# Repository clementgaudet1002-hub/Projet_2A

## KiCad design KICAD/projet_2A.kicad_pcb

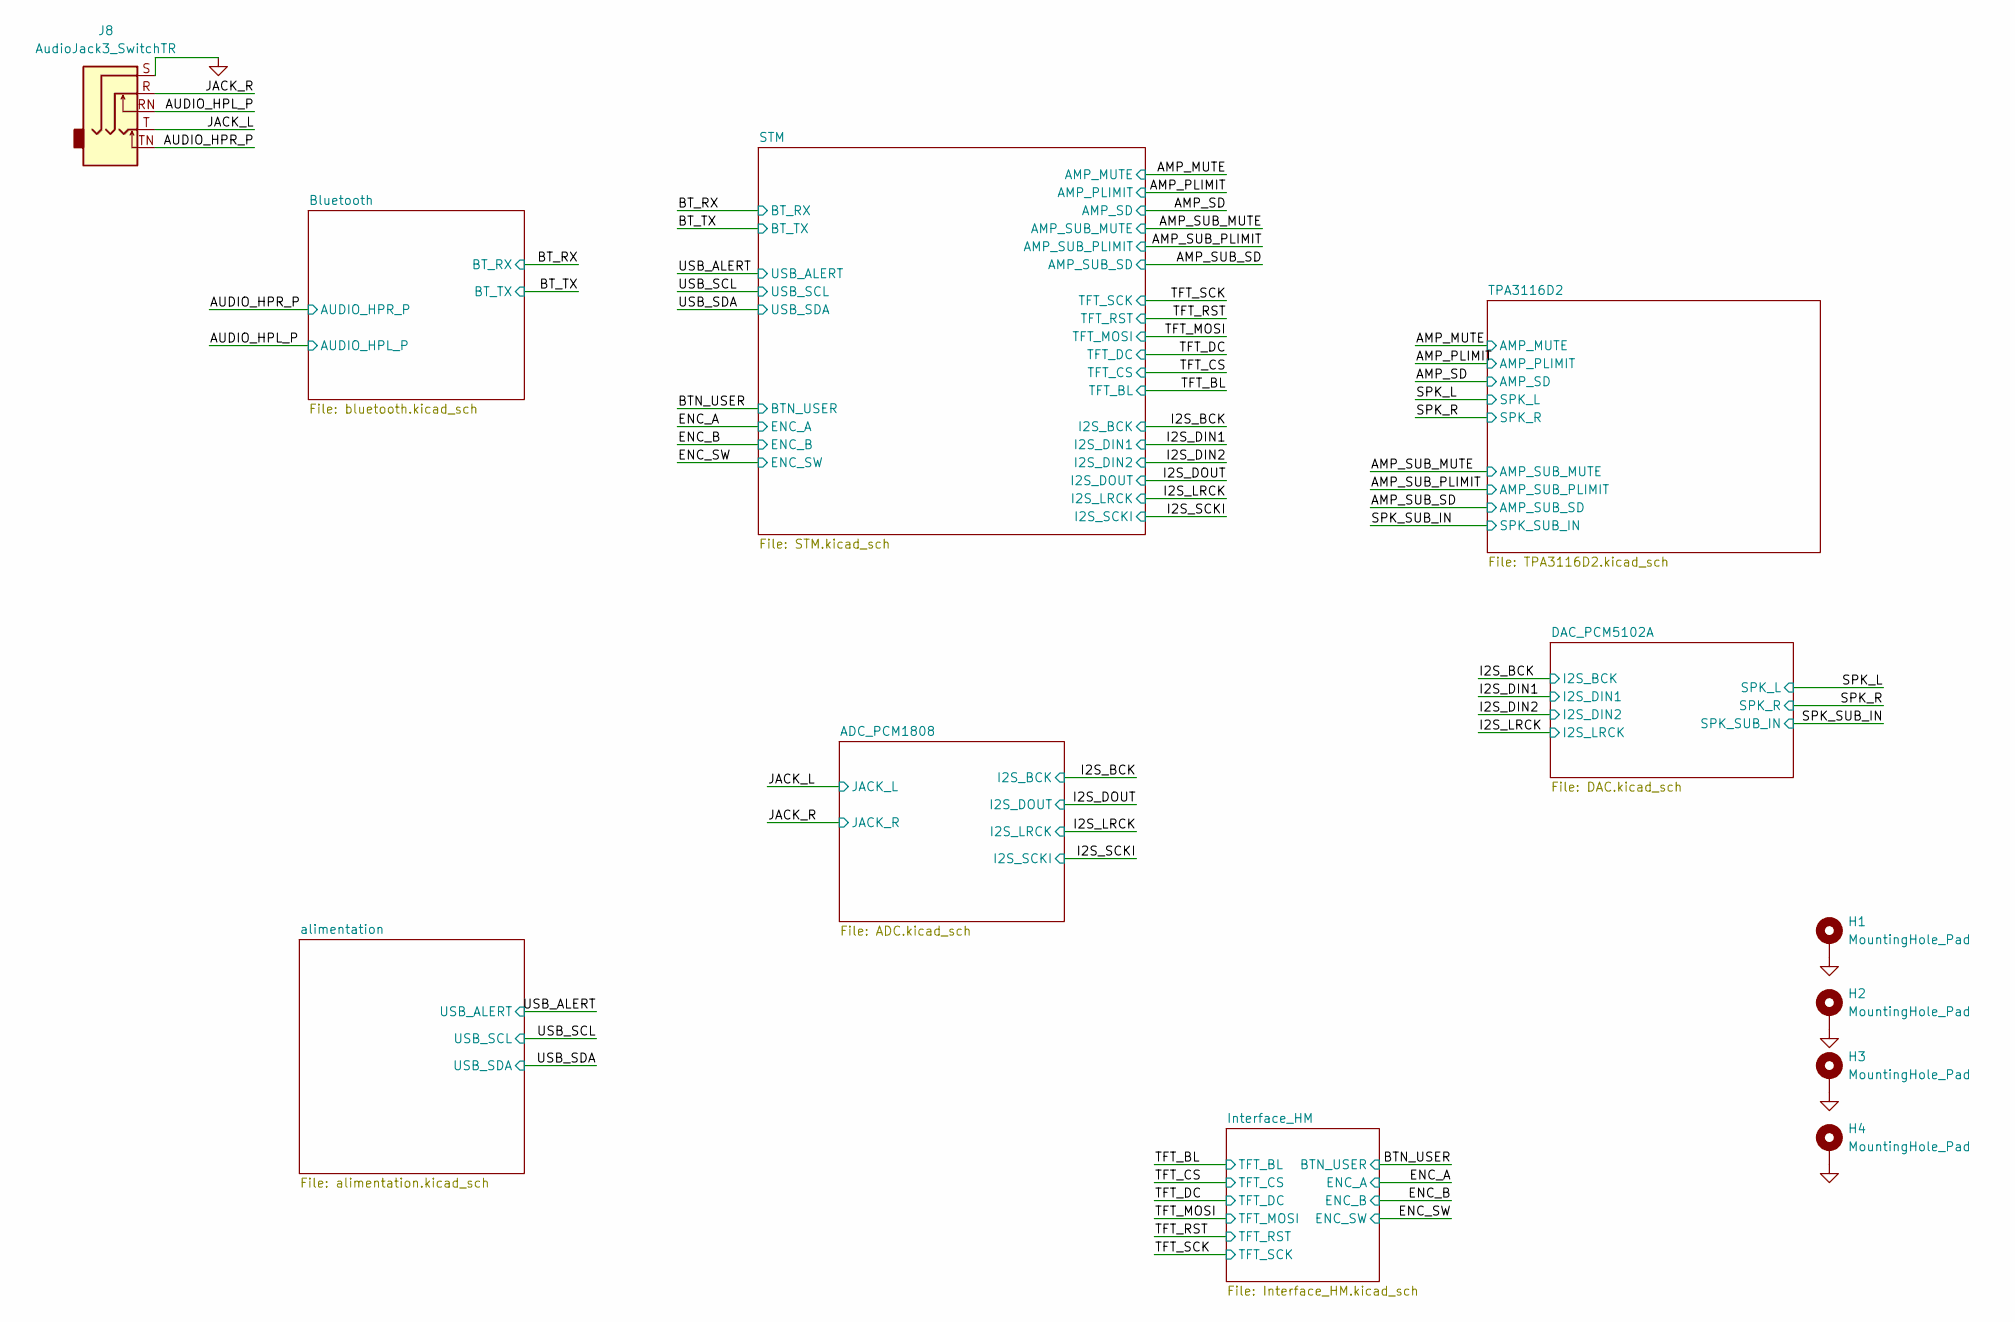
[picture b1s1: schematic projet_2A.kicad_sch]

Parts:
H1, H2, H3, H4: MountingHole_Pad; MountingHole_2.2mm_M2_Pad_TopBottom
J8: AudioJack3_SwitchTR; Jack_3.5mm_Ledino_KB3SPRS_Horizontal

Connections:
/AUDIO_HPL_P: J8.RN; also elsewhere on the board
/AUDIO_HPR_P: J8.TN; also elsewhere on the board
/JACK_L: J8.T; also elsewhere on the board
/JACK_R: J8.R; also elsewhere on the board
GND: H1.1 (1_1), H2.1 (1_1), H3.1 (1_1), H4.1 (1_1), J8.S; also elsewhere on the board

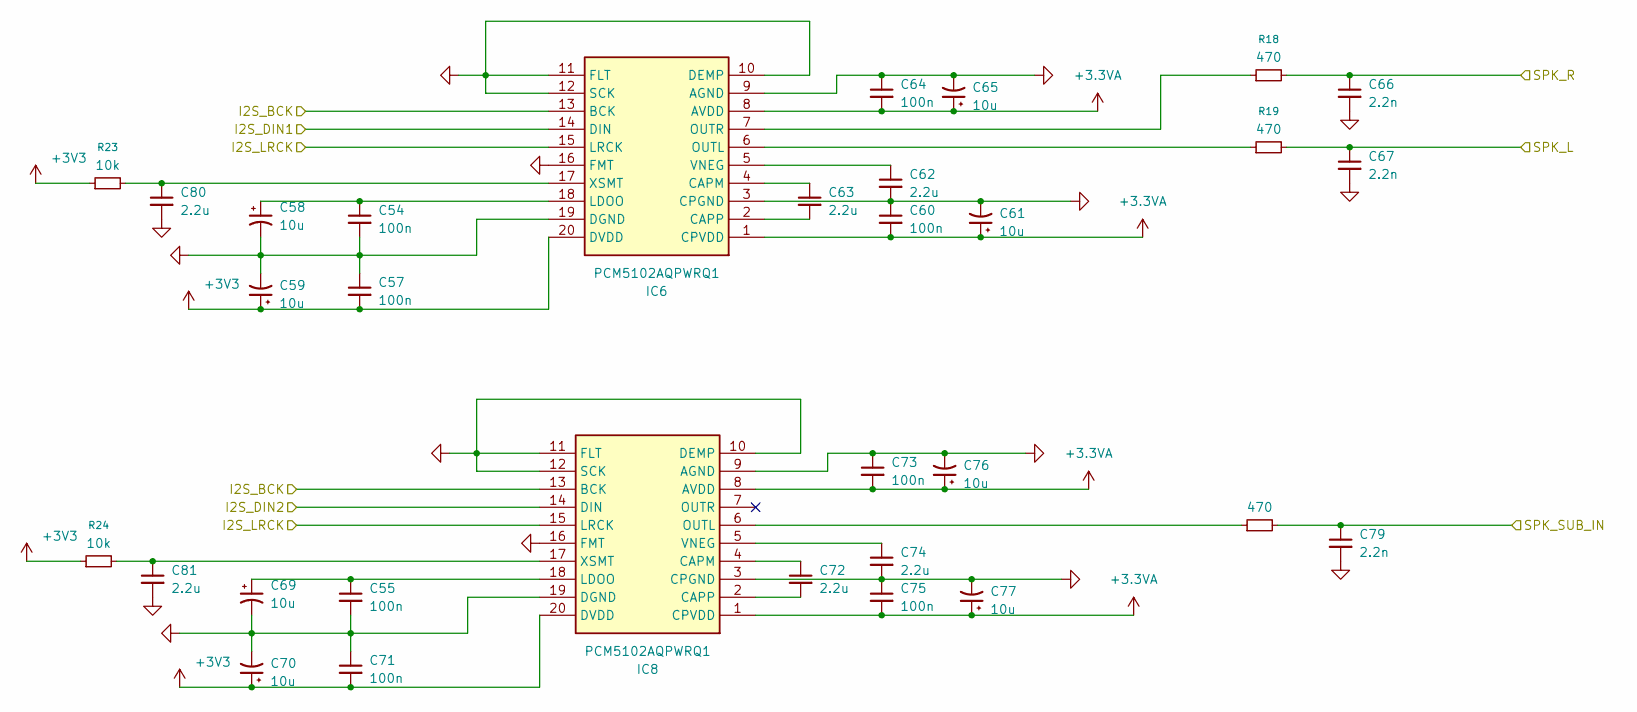
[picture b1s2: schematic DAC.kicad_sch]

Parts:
C54, C55, C57, C60, C64, C71, C73, C75: 100n; C_0603_1608Metric
C58, C59, C61, C65, C69, C70, C76, C77: 10u; C_1206_3216Metric
C62, C63, C72, C74, C80, C81: 2.2u; C_1206_3216Metric
C66, C67, C79: 2.2n; C_0603_1608Metric
IC6, IC8: PCM5102AQPWRQ1; Manufacturer_Part_Number PCM5102AQPWRQ1; Mouser Part Number 595-PCM5102AQPWRQ1
R18, R19, R22: 470; R_0603_1608Metric
R23, R24: 10k; R_0603_1608Metric

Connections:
+3.3VA: C60.2, C61.1, C64.2, C65.1, C73.2, C75.2, C76.1, C77.1, IC6.1 (CPVDD), IC6.8 (AVDD), IC8.1 (CPVDD), IC8.8 (AVDD); also elsewhere on the board
+3V3: C57.2, C59.1, C70.1, C71.2, IC6.20 (DVDD), IC8.20 (DVDD), R23.1, R24.1; also elsewhere on the board
/I2S_BCK: IC6.13 (BCK), IC8.13 (BCK); also elsewhere on the board
/I2S_DIN1: IC6.14 (DIN); also elsewhere on the board
/I2S_DIN2: IC8.14 (DIN); also elsewhere on the board
/I2S_LRCK: IC6.15 (LRCK), IC8.15 (LRCK); also elsewhere on the board
/SPK_L: C67.1, R19.2; also elsewhere on the board
/SPK_R: C66.1, R18.2; also elsewhere on the board
/SPK_SUB_IN: C79.1, R22.2; also elsewhere on the board
GND: C54.2, C55.2, C57.1, C58.2, C59.2, C60.1, C61.2, C62.2, C64.1, C65.2, C66.2, C67.2, C69.2, C70.2, C71.1, C73.1, C74.2, C75.1, C76.2, C77.2, C79.2, C80.2, C81.2, IC6.3 (CPGND), IC6.9 (AGND), IC6.10 (DEMP), IC6.11 (FLT), IC6.12 (SCK), IC6.16 (FMT), IC6.19 (DGND), IC8.3 (CPGND), IC8.9 (AGND), IC8.10 (DEMP), IC8.11 (FLT), IC8.12 (SCK), IC8.16 (FMT), IC8.19 (DGND); also elsewhere on the board
unnamed: C63.1, IC6.4 (CAPM)
unnamed: C63.2, IC6.2 (CAPP)
unnamed: C54.1, C58.1, IC6.18 (LDOO)
unnamed: IC6.6 (OUTL), R19.1
unnamed: IC6.7 (OUTR), R18.1
unnamed: C62.1, IC6.5 (VNEG)
unnamed: C80.1, IC6.17 (XSMT), R23.2
unnamed: C72.1, IC8.4 (CAPM)
unnamed: C72.2, IC8.2 (CAPP)
unnamed: C55.1, C69.1, IC8.18 (LDOO)
unnamed: IC8.6 (OUTL), R22.1
unnamed: C74.1, IC8.5 (VNEG)
unnamed: C81.1, IC8.17 (XSMT), R24.2

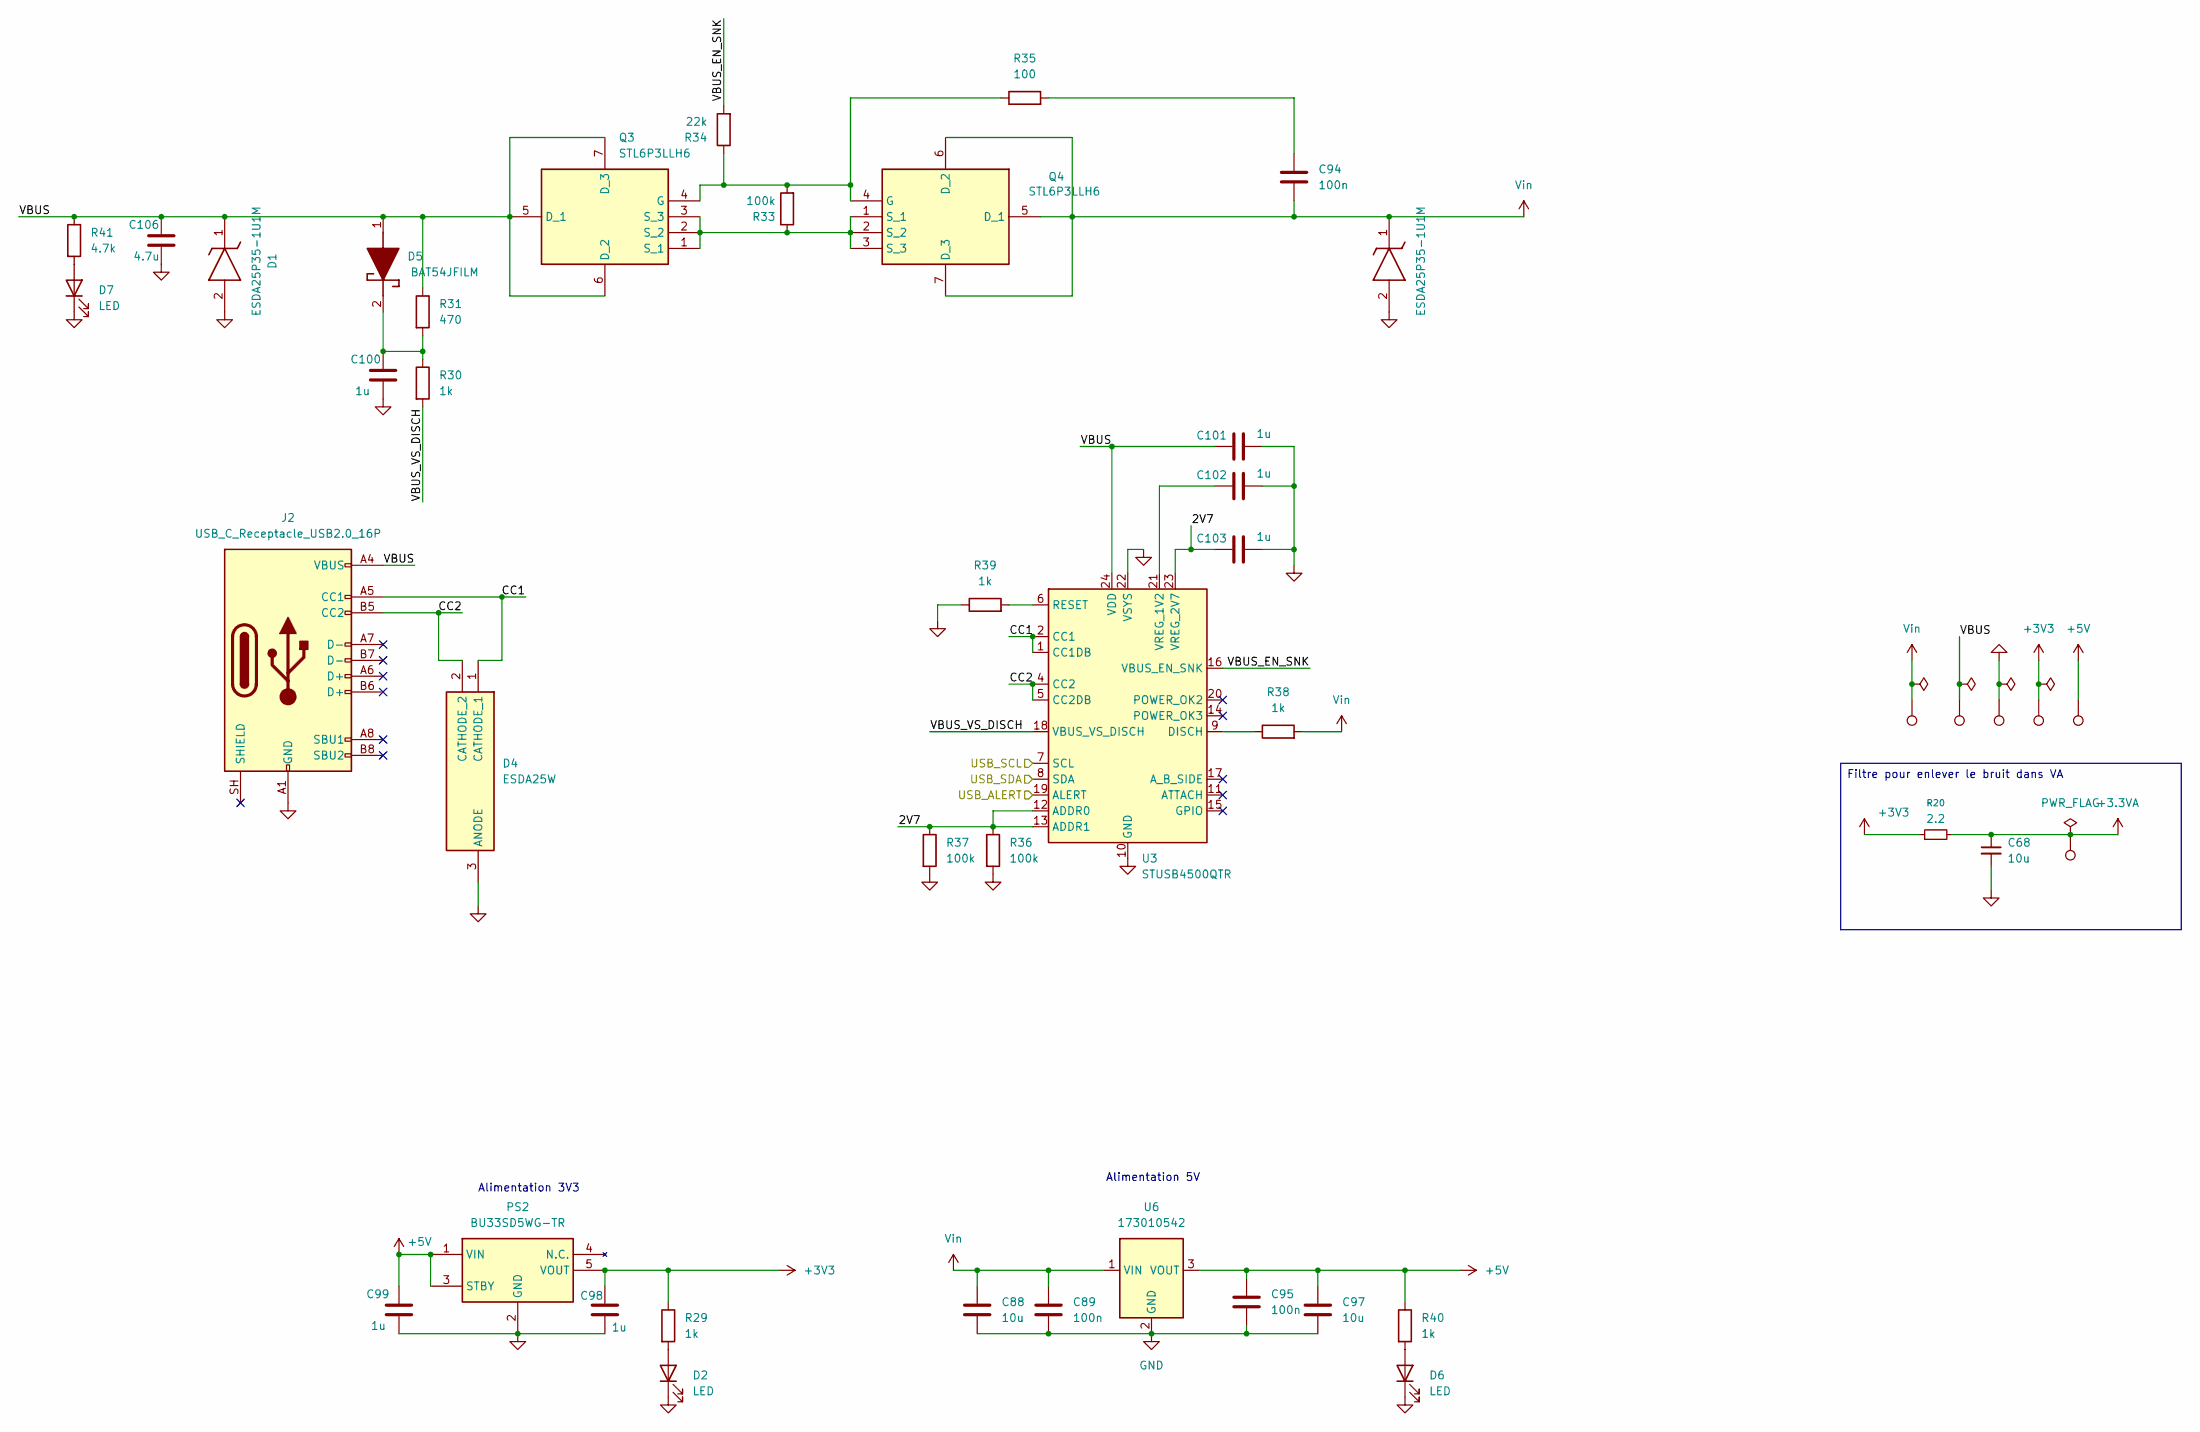
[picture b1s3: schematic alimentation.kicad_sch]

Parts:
C68, C88, C97: 10u; C_1206_3216Metric
C89, C94, C95: 100n; C_0603_1608Metric
C98, C99, C100, C101, C102, C103: 1u; C_0603_1608Metric
C106: 4.7u; C_0603_1608Metric
D1, D3: ESDA25P35-1U1M; ESDA25P351U1M; Mouser Part Number 511-ESDA25P35-1U1M
D2, D6, D7: LED; LED_0603_1608Metric
D4: ESDA25W; Mouser Part Number 511-ESDA25W
D5: BAT54JFILM; Mouser Part Number 511-BAT54JFILM
J2: USB_C_Receptacle_USB2.0_16P; USB_C_Receptacle_GCT_USB4105-xx-A_16P_TopMnt_Horizontal
PS2: BU33SD5WG-TR; Manufacturer_Part_Number BU33SD5WG-TR; Mouser Part Number 755-BU33SD5WG-TR
Q3, Q4: STL6P3LLH6; STL8N10F7; Mouser Part Number 511-STL6P3LLH6
R20: 2.2; R_0603_1608Metric
R29, R30, R38, R39, R40: 1k; R_0603_1608Metric
R31: 470; R_0603_1608Metric
R33, R36, R37: 100k; R_0603_1608Metric
R34: 22k; R_0603_1608Metric
R35: 100; R_0603_1608Metric
R41: 4.7k; R_1206_3216Metric
TP2, TP4, TP5, TP6, TP7, TP8: TestPoint; TestPoint_Pad_D1.5mm
U3: STUSB4500QTR; QFN-24-1EP_4x4mm_P0.5mm_EP2.7x2.7mm
U6: 173010542; U_Wurth_MagIC-FDSM_173010x42

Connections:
+3.3VA: C68.1, R20.2, TP8.1 (1_1); also elsewhere on the board
+3V3: C98.1, PS2.5 (VOUT), R20.1, R29.1, TP6.1 (1_1); also elsewhere on the board
+5V: C95.1, C97.1, C99.1, PS2.1 (VIN), PS2.3 (STBY), R40.1, TP7.1 (1_1), U6.3 (VOUT); also elsewhere on the board
/USB_ALERT: U3.19 (ALERT); also elsewhere on the board
/USB_SCL: U3.7 (SCL); also elsewhere on the board
/USB_SDA: U3.8 (SDA); also elsewhere on the board
/alimentation/2V7: C103.1, R36.1, R37.1, U3.12 (ADDR0), U3.13 (ADDR1), U3.23 (VREG_2V7)
/alimentation/CC1: D4.1 (CATHODE_1), J2.A5 (CC1), U3.1 (CC1DB), U3.2 (CC1)
/alimentation/CC2: D4.2 (CATHODE_2), J2.B5 (CC2), U3.4 (CC2), U3.5 (CC2DB)
/alimentation/VBUS: C101.1, C106.1, D1.1 (K), D5.1 (A), J2.A4 (VBUS), J2.A9 (VBUS), J2.B4 (VBUS), J2.B9 (VBUS), Q3.5 (D_1), Q3.6 (D_2), Q3.7 (D_3), R31.1, R41.1, TP4.1 (1_1), U3.24 (VDD)
/alimentation/VBUS_EN_SNK: R34.2, U3.16 (VBUS_EN_SNK)
/alimentation/VBUS_VS_DISCH: R30.2, U3.18 (VBUS_VS_DISCH)
GND: C68.2, C88.2, C89.2, C95.2, C97.2, C98.2, C99.2, C100.2, C101.2, C102.2, C103.2, C106.2, D1.2 (A), D2.1 (K), D3.2 (A), D4.3 (ANODE), D6.1 (K), D7.1 (K), J2.A1 (GND), J2.A12 (GND), J2.B1 (GND), J2.B12 (GND), PS2.2 (GND), R36.2, R37.2, R39.1, TP5.1 (1_1), U3.10 (GND), U3.22 (VSYS), U3.25 (GND), U6.2 (GND); also elsewhere on the board
unnamed: C94.2, R35.2
unnamed: D2.2 (A), R29.2
unnamed: C100.1, D5.2 (K), R30.1, R31.2
unnamed: D6.2 (A), R40.2
unnamed: D7.2 (A), R41.2
unnamed: Q3.4 (G), Q4.4 (G), R33.2, R34.1, R35.1
unnamed: Q3.1 (S_1), Q3.2 (S_2), Q3.3 (S_3), Q4.1 (S_1), Q4.2 (S_2), Q4.3 (S_3), R33.1
unnamed: R38.1, U3.9 (DISCH)
unnamed: R39.2, U3.6 (RESET)
unnamed: C102.1, U3.21 (VREG_1V2)
Vin: C88.1, C89.1, C94.1, D3.1 (K), Q4.5 (D_1), Q4.6 (D_2), Q4.7 (D_3), R38.2, TP2.1 (1_1), U6.1 (VIN); also elsewhere on the board

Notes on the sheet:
Alimentation 5V
Alimentation 3V3
Filtre pour enlever le bruit dans VA

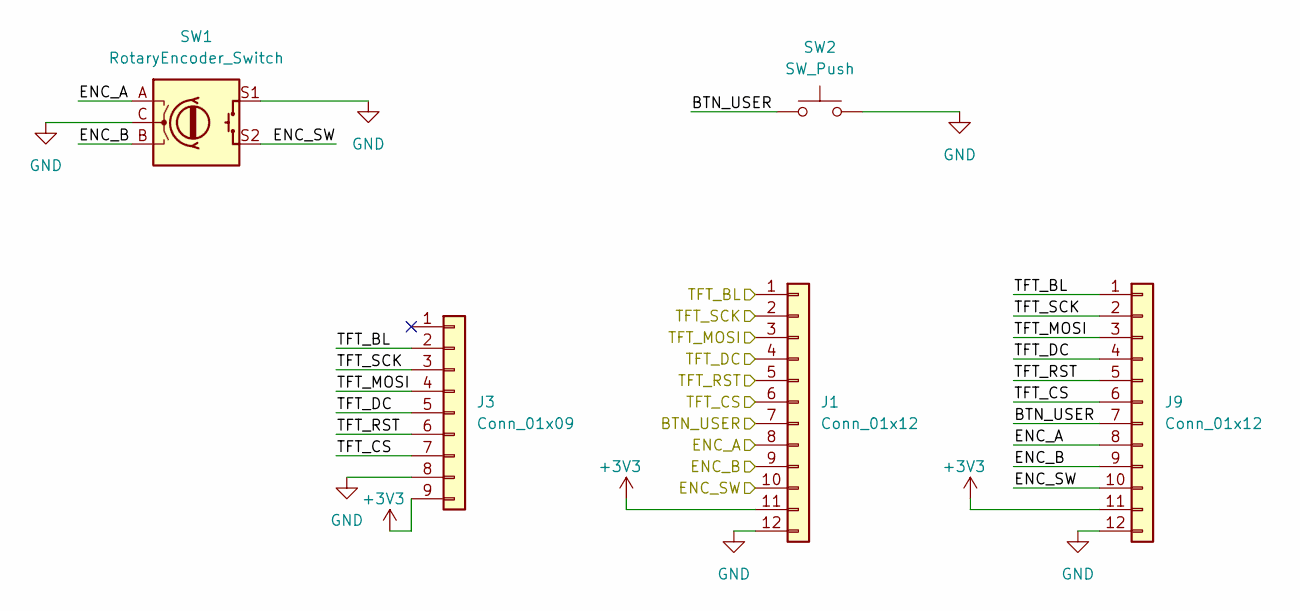
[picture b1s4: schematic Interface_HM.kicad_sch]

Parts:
J1, J9: Conn_01x12; PinHeader_1x12_P2.54mm_Vertical
J3: Conn_01x09; PinHeader_1x09_P2.54mm_Vertical
SW1: RotaryEncoder_Switch; RotaryEncoder_Alps_EC11E-Switch_Vertical_H20mm_CircularMoun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
SW2: SW_Push; SW_PUSH_6mm

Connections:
+3V3: J1.11, J3.9, J9.11; also elsewhere on the board
/BTN_USER: J1.7, J9.7, SW2.1; also elsewhere on the board
/ENC_A: J1.8, J9.8, SW1.A; also elsewhere on the board
/ENC_B: J1.9, J9.9, SW1.B; also elsewhere on the board
/ENC_SW: J1.10, J9.10, SW1.S2; also elsewhere on the board
/TFT_BL: J1.1, J3.2, J9.1; also elsewhere on the board
/TFT_CS: J1.6, J3.7, J9.6; also elsewhere on the board
/TFT_DC: J1.4, J3.5, J9.4; also elsewhere on the board
/TFT_MOSI: J1.3, J3.4, J9.3; also elsewhere on the board
/TFT_RST: J1.5, J3.6, J9.5; also elsewhere on the board
/TFT_SCK: J1.2, J3.3, J9.2; also elsewhere on the board
GND: J1.12, J3.8, J9.12, SW1.C, SW1.S1, SW2.2; also elsewhere on the board

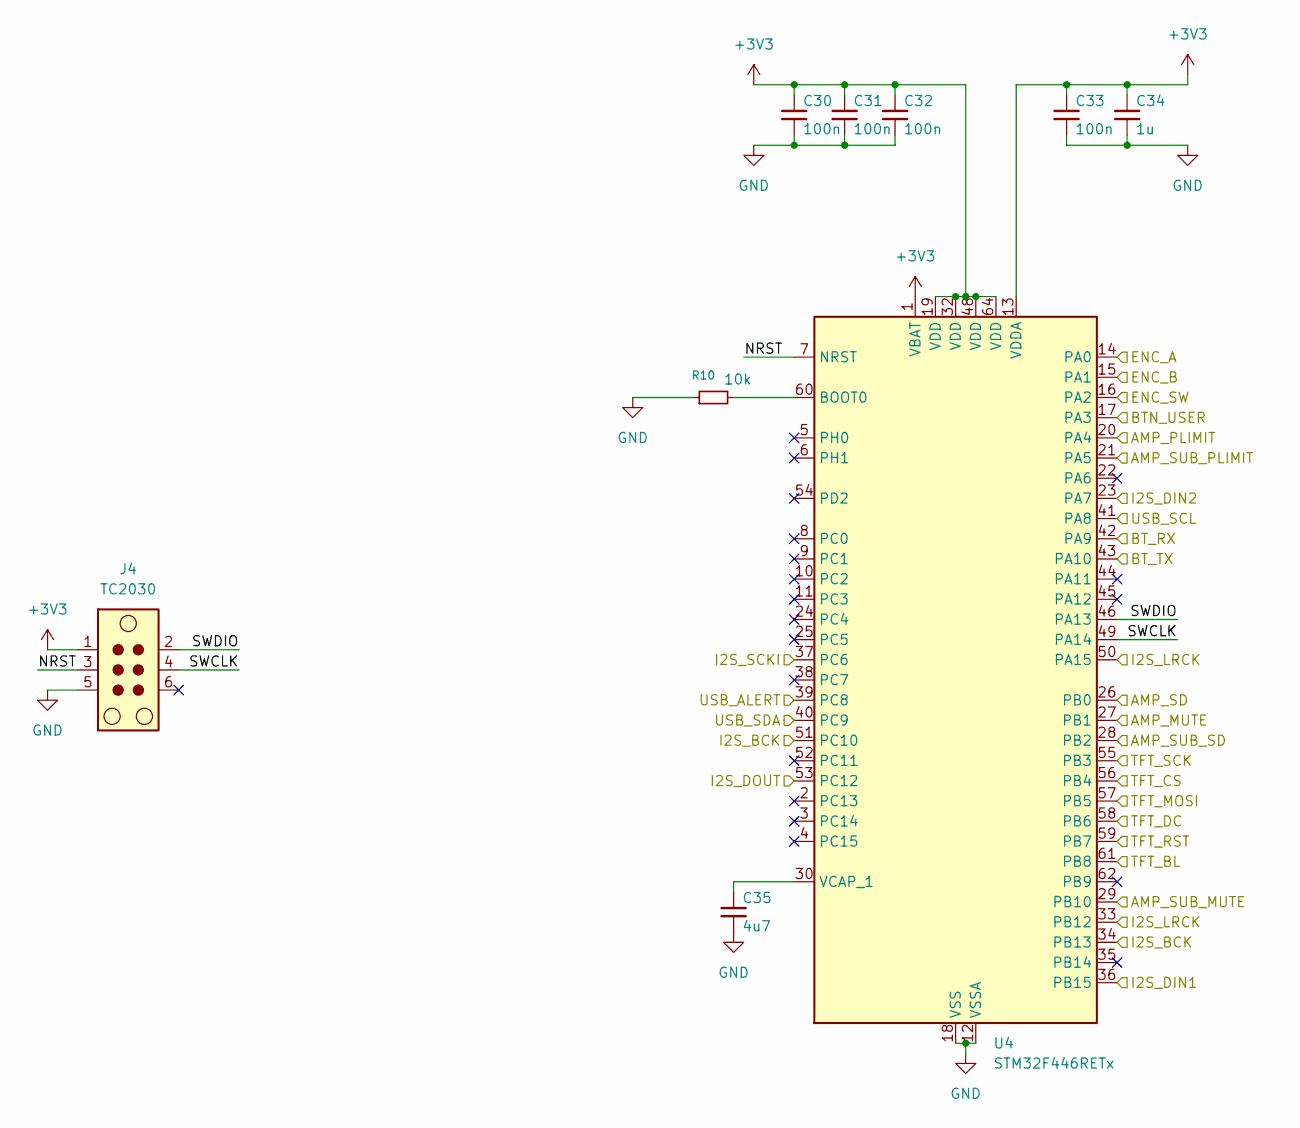
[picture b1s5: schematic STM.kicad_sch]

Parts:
C30, C31, C32, C33: 100n; C_0603_1608Metric
C34: 1u; C_0603_1608Metric
C35: 4u7; C_1206_3216Metric
J4: TC2030; Tag-Connect_TC2030-IDC-NL_2x03_P1.27mm_Vertical
R10: 10k; R_0603_1608Metric
U4: STM32F446RETx; LQFP-64_10x10mm_P0.5mm

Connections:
+3V3: C30.1, C31.1, C32.1, C33.1, C34.1, J4.1, U4.1 (VBAT), U4.13 (VDDA), U4.19 (VDD), U4.32 (VDD), U4.48 (VDD), U4.64 (VDD); also elsewhere on the board
/AMP_MUTE: U4.27 (PB1); also elsewhere on the board
/AMP_PLIMIT: U4.20 (PA4); also elsewhere on the board
/AMP_SD: U4.26 (PB0); also elsewhere on the board
/AMP_SUB_MUTE: U4.29 (PB10); also elsewhere on the board
/AMP_SUB_PLIMIT: U4.21 (PA5); also elsewhere on the board
/AMP_SUB_SD: U4.28 (PB2); also elsewhere on the board
/BTN_USER: U4.17 (PA3); also elsewhere on the board
/BT_RX: U4.42 (PA9); also elsewhere on the board
/BT_TX: U4.43 (PA10); also elsewhere on the board
/ENC_A: U4.14 (PA0); also elsewhere on the board
/ENC_B: U4.15 (PA1); also elsewhere on the board
/ENC_SW: U4.16 (PA2); also elsewhere on the board
/I2S_BCK: U4.34 (PB13), U4.51 (PC10); also elsewhere on the board
/I2S_DIN1: U4.36 (PB15); also elsewhere on the board
/I2S_DIN2: U4.23 (PA7); also elsewhere on the board
/I2S_DOUT: U4.53 (PC12); also elsewhere on the board
/I2S_LRCK: U4.33 (PB12), U4.50 (PA15); also elsewhere on the board
/I2S_SCKI: U4.37 (PC6); also elsewhere on the board
/STM/NRST: J4.3, U4.7 (NRST)
/STM/SWCLK: J4.4, U4.49 (PA14)
/STM/SWDIO: J4.2, U4.46 (PA13)
/TFT_BL: U4.61 (PB8); also elsewhere on the board
/TFT_CS: U4.56 (PB4); also elsewhere on the board
/TFT_DC: U4.58 (PB6); also elsewhere on the board
/TFT_MOSI: U4.57 (PB5); also elsewhere on the board
/TFT_RST: U4.59 (PB7); also elsewhere on the board
/TFT_SCK: U4.55 (PB3); also elsewhere on the board
/USB_ALERT: U4.39 (PC8); also elsewhere on the board
/USB_SCL: U4.41 (PA8); also elsewhere on the board
/USB_SDA: U4.40 (PC9); also elsewhere on the board
GND: C30.2, C31.2, C32.2, C33.2, C34.2, C35.2, J4.5, R10.1, U4.12 (VSSA), U4.18 (VSS), U4.31 (VSS), U4.47 (VSS), U4.63 (VSS); also elsewhere on the board
unnamed: R10.2, U4.60 (BOOT0)
unnamed: C35.1, U4.30 (VCAP_1)

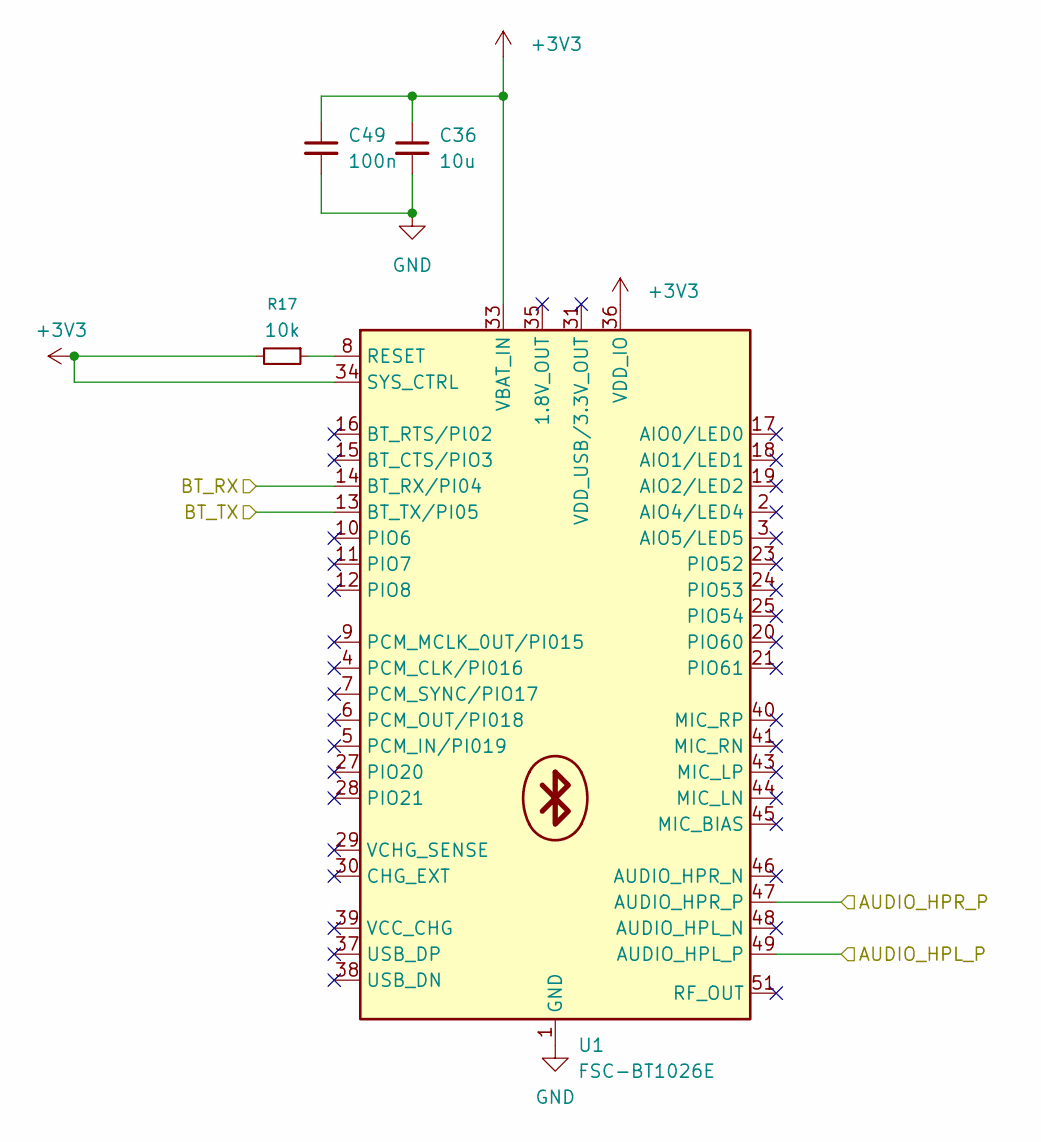
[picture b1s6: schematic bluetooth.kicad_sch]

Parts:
C36: 10u; C_1206_3216Metric
C49: 100n; C_0603_1608Metric
R17: 10k; R_0603_1608Metric
U1: FSC-BT1026E; FSC-BT1026x

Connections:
+3V3: C36.1, C49.1, R17.2, U1.33 (VBAT_IN), U1.34 (SYS_CTRL), U1.36 (VDD_IO); also elsewhere on the board
/AUDIO_HPL_P: U1.49 (AUDIO_HPL_P); also elsewhere on the board
/AUDIO_HPR_P: U1.47 (AUDIO_HPR_P); also elsewhere on the board
/BT_RX: U1.14 (BT_RX/PI04); also elsewhere on the board
/BT_TX: U1.13 (BT_TX/PI05); also elsewhere on the board
GND: C36.2, C49.2, U1.1 (GND), U1.22 (GND), U1.32 (GND), U1.50 (GND), U1.52 (GND); also elsewhere on the board
unnamed: R17.1, U1.8 (RESET)

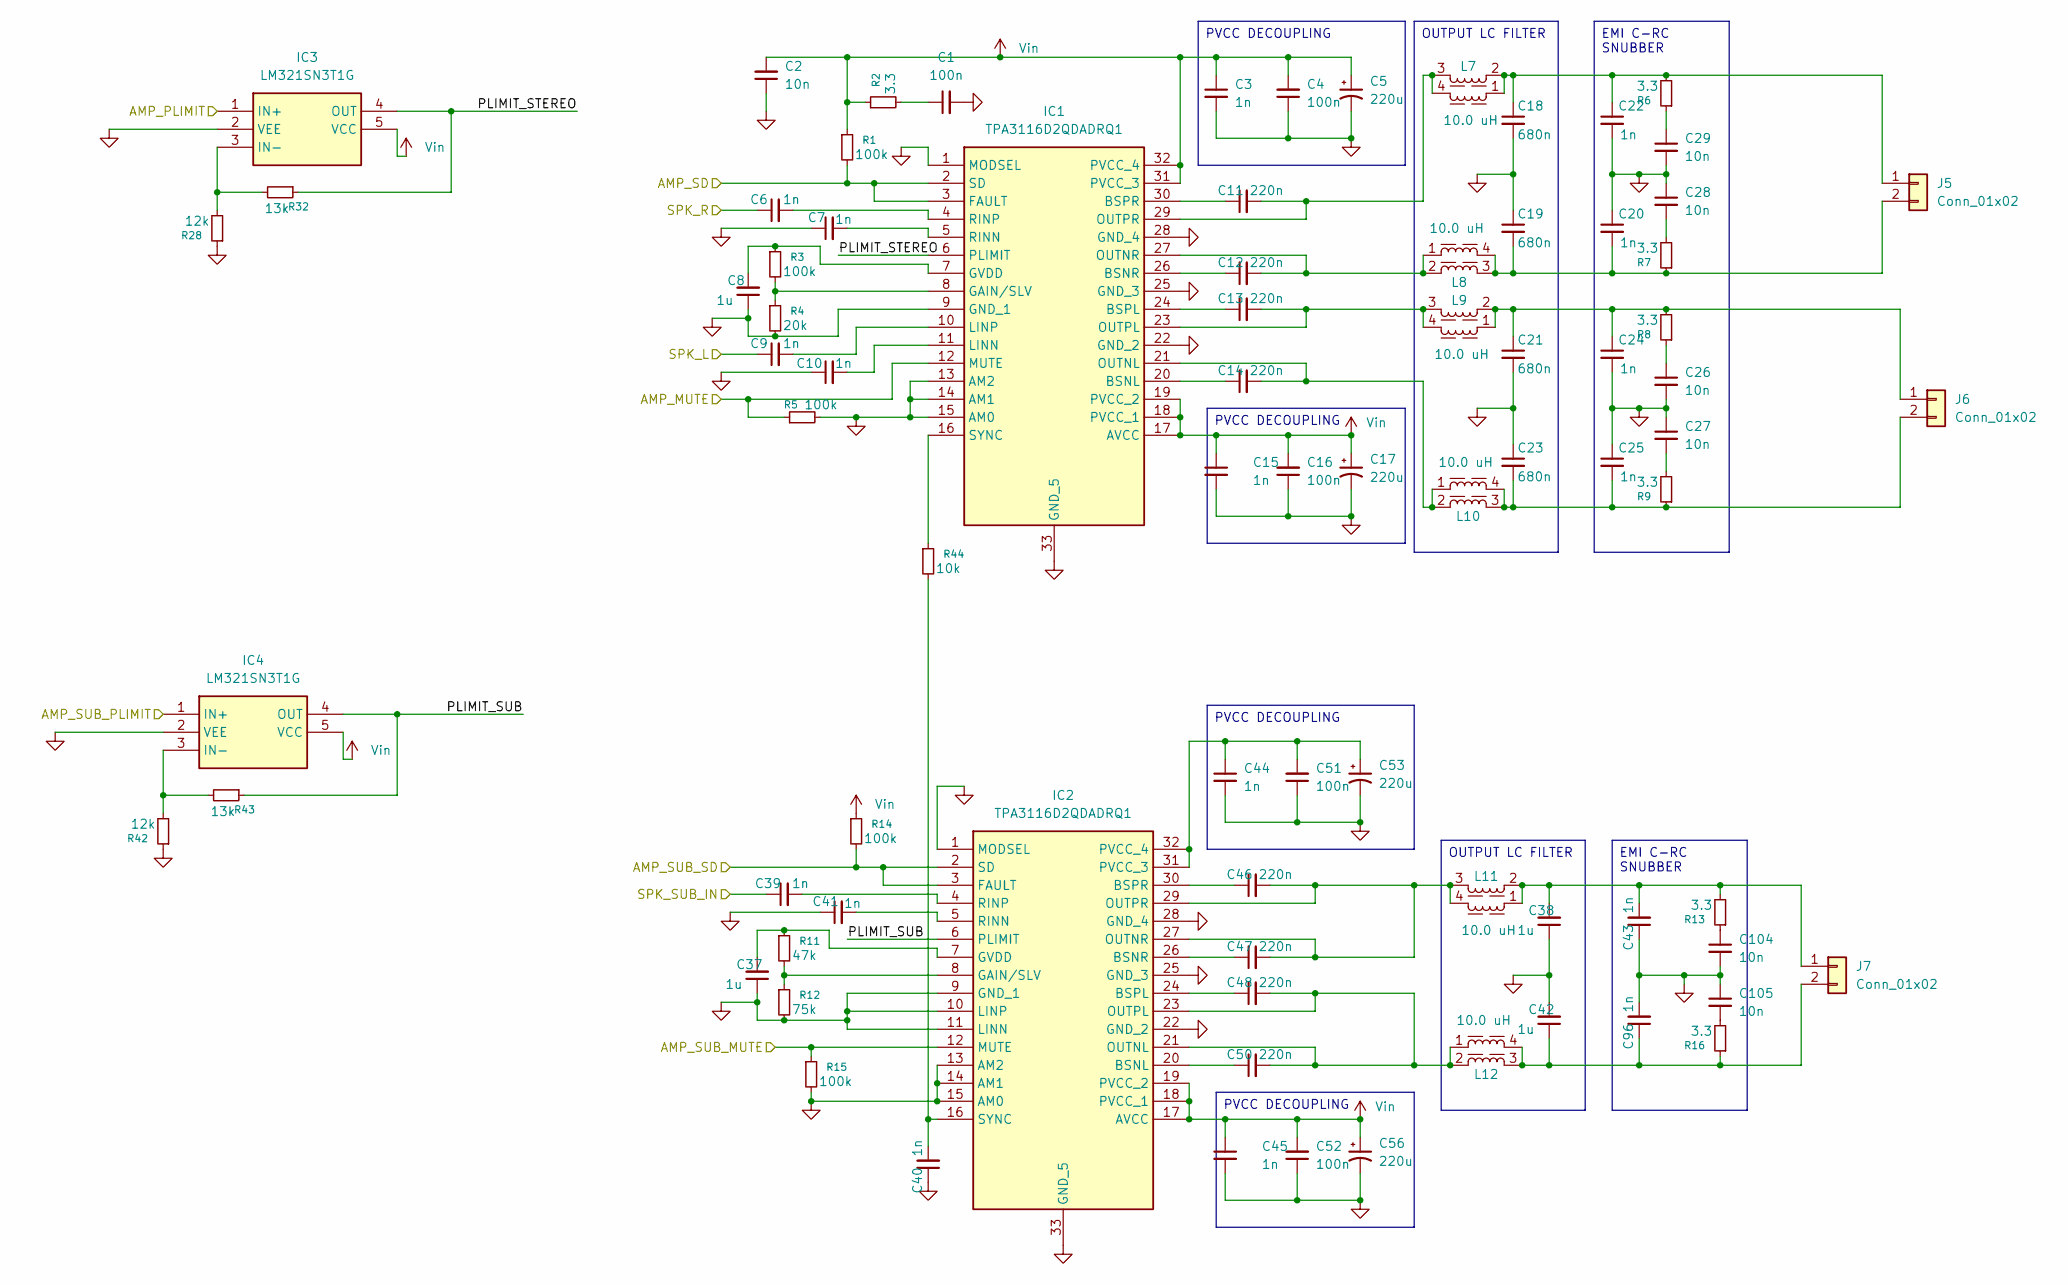
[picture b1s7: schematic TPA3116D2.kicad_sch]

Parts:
C1, C4, C16, C51, C52: 100n; C_0603_1608Metric
C2, C26, C27, C28, C29, C104, C105: 10n; C_0603_1608Metric
C3, C6, C7, C9, C10, C15, C20, C22, C24, C25, C39, C40, C41, C43, C44, C45, C96: 1n; C_0603_1608Metric
C5, C17, C53, C56: 220u; CP_Radial_D6.3mm_P2.50mm
C8, C37, C38, C42: 1u; C_0603_1608Metric
C11, C12, C13, C14, C46, C47, C48, C50: 220n; C_0603_1608Metric
C18, C19, C21, C23: 680n; C_0603_1608Metric
IC1, IC2: TPA3116D2QDADRQ1; Mouser Part Number 595-TPA3116D2QDADRQ1
IC3, IC4: LM321SN3T1G; Mouser Part Number 863-LM321SN3T1G
J5, J6, J7: Conn_01x02; TerminalBlock_Phoenix_MKDS-1,5-2-5.08_1x02_P5.08mm_Horizont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
L7, L8, L9, L10, L11, L12: 10.0 uH; L_Wurth_WE-LHMD-1213; Part Number 74434301213100
R1, R3, R5, R14, R15: 100k; R_0603_1608Metric
R2, R6, R7, R8, R9, R13, R16: 3.3; R_0603_1608Metric
R4: 20k; R_0603_1608Metric
R11: 47k; R_0603_1608Metric
R12: 75k; R_0603_1608Metric
R28, R42: 12k; R_0603_1608Metric
R32, R43: 13k; R_0603_1608Metric
R44: 10k; R_0603_1608Metric

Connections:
/AMP_MUTE: IC1.12 (MUTE), R5.1; also elsewhere on the board
/AMP_PLIMIT: IC3.1 (IN+); also elsewhere on the board
/AMP_SD: IC1.2 (SD), IC1.3 (FAULT), R1.2; also elsewhere on the board
/AMP_SUB_MUTE: IC2.12 (MUTE), R15.1; also elsewhere on the board
/AMP_SUB_PLIMIT: IC4.1 (IN+); also elsewhere on the board
/AMP_SUB_SD: IC2.2 (SD), IC2.3 (FAULT), R14.2; also elsewhere on the board
/SPK_L: C9.1; also elsewhere on the board
/SPK_R: C6.1; also elsewhere on the board
/SPK_SUB_IN: C39.1; also elsewhere on the board
/TPA3116D2/PLIMIT_STEREO: IC1.6 (PLIMIT), IC3.4 (OUT), R32.1
/TPA3116D2/PLIMIT_SUB: IC2.6 (PLIMIT), IC4.4 (OUT), R43.1
GND: C1.2, C2.1, C3.2, C4.1, C5.2, C7.1, C8.1, C10.1, C15.2, C16.1, C17.2, C18.2, C19.1, C20.1, C21.2, C22.2, C23.1, C24.2, C25.1, C26.2, C27.1, C28.1, C29.2, C37.1, C38.1, C40.1, C41.1, C42.2, C43.1, C44.2, C45.2, C51.1, C52.1, C53.2, C56.2, C96.2, C104.2, C105.1, IC1.1 (MODSEL), IC1.9 (GND_1), IC1.13 (AM2), IC1.14 (AM1), IC1.15 (AM0), IC1.22 (GND_2), IC1.25 (GND_3), IC1.28 (GND_4), IC1.33 (GND_5), IC2.1 (MODSEL), IC2.9 (GND_1), IC2.10 (LINP), IC2.11 (LINN), IC2.13 (AM2), IC2.14 (AM1), IC2.15 (AM0), IC2.22 (GND_2), IC2.25 (GND_3), IC2.28 (GND_4), IC2.33 (GND_5), IC3.2 (VEE), IC4.2 (VEE), R4.2, R5.2, R12.2, R15.2, R28.1, R42.1; also elsewhere on the board
unnamed: C1.1, R2.2
unnamed: C26.1, R8.1
unnamed: C27.2, R9.2
unnamed: C28.2, R7.2
unnamed: C29.1, R6.1
unnamed: C104.1, R13.1
unnamed: C105.2, R16.2
unnamed: C14.1, IC1.20 (BSNL)
unnamed: C12.1, IC1.26 (BSNR)
unnamed: C13.1, IC1.24 (BSPL)
unnamed: C11.1, IC1.30 (BSPR)
unnamed: IC1.8 (GAIN/SLV), R3.2, R4.1
unnamed: C8.2, IC1.7 (GVDD), R3.1
unnamed: C10.2, IC1.11 (LINN)
unnamed: C9.2, IC1.10 (LINP)
unnamed: C14.2, IC1.21 (OUTNL), L10.1, L10.2
unnamed: C12.2, IC1.27 (OUTNR), L8.1, L8.2
unnamed: C13.2, IC1.23 (OUTPL), L9.3, L9.4
unnamed: C11.2, IC1.29 (OUTPR), L7.3, L7.4
unnamed: C7.2, IC1.5 (RINN)
unnamed: C6.2, IC1.4 (RINP)
unnamed: IC1.16 (SYNC), R44.1
unnamed: C50.1, IC2.20 (BSNL)
unnamed: C47.1, IC2.26 (BSNR)
unnamed: C48.1, IC2.24 (BSPL)
unnamed: C46.1, IC2.30 (BSPR)
unnamed: IC2.8 (GAIN/SLV), R11.2, R12.1
unnamed: C37.2, IC2.7 (GVDD), R11.1
unnamed: C48.2, C50.2, IC2.21 (OUTNL), IC2.23 (OUTPL), L12.1, L12.2
unnamed: C46.2, C47.2, IC2.27 (OUTNR), IC2.29 (OUTPR), L11.3, L11.4
unnamed: C44.1, C51.2, C53.1, IC2.31 (PVCC_3), IC2.32 (PVCC_4)
unnamed: C41.2, IC2.5 (RINN)
unnamed: C39.2, IC2.4 (RINP)
unnamed: C40.2, IC2.16 (SYNC), R44.2
unnamed: IC3.3 (IN-), R28.2, R32.2
unnamed: IC4.3 (IN-), R42.2, R43.2
unnamed: C18.1, C22.1, J5.1, L7.1, L7.2, R6.2
unnamed: C19.2, C20.2, J5.2, L8.3, L8.4, R7.1
unnamed: C21.1, C24.1, J6.1, L9.1, L9.2, R8.2
unnamed: C23.2, C25.2, J6.2, L10.3, L10.4, R9.1
unnamed: C38.2, C43.2, J7.1, L11.1, L11.2, R13.2
unnamed: C42.1, C96.1, J7.2, L12.3, L12.4, R16.1
Vin: C2.2, C3.1, C4.2, C5.1, C15.1, C16.2, C17.1, C45.1, C52.2, C56.1, IC1.17 (AVCC), IC1.18 (PVCC_1), IC1.19 (PVCC_2), IC1.31 (PVCC_3), IC1.32 (PVCC_4), IC2.17 (AVCC), IC2.18 (PVCC_1), IC2.19 (PVCC_2), IC3.5 (VCC), IC4.5 (VCC), R1.1, R2.1, R14.1; also elsewhere on the board

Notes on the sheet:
EMI C-RC SNUBBER
OUTPUT LC FILTER
PVCC DECOUPLING

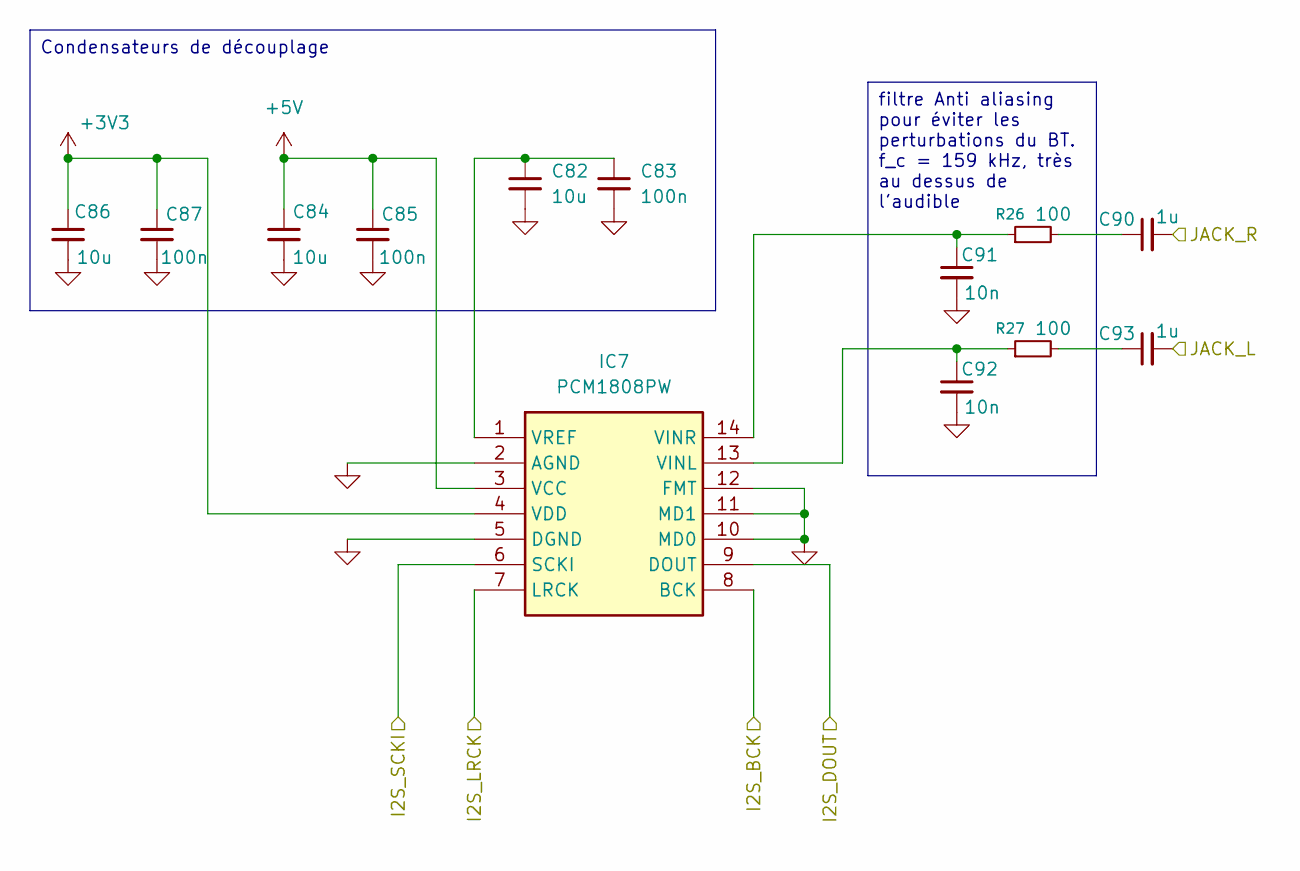
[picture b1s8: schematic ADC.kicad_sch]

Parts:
C82, C84, C86: 10u; C_0402_1005Metric
C83, C85, C87: 100n; C_0402_1005Metric
C90, C93: 1u; C_0402_1005Metric
C91, C92: 10n; C_0402_1005Metric
IC7: PCM1808PW; Manufacturer_Part_Number PCM1808PW; Mouser Part Number 595-PCM1808PW
R26, R27: 100

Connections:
+3V3: C86.1, C87.1, IC7.4 (VDD); also elsewhere on the board
+5V: C84.1, C85.1, IC7.3 (VCC); also elsewhere on the board
/I2S_BCK: IC7.8 (BCK); also elsewhere on the board
/I2S_DOUT: IC7.9 (DOUT); also elsewhere on the board
/I2S_LRCK: IC7.7 (LRCK); also elsewhere on the board
/I2S_SCKI: IC7.6 (SCKI); also elsewhere on the board
/JACK_L: C93.2; also elsewhere on the board
/JACK_R: C90.2; also elsewhere on the board
GND: C82.2, C83.2, C84.2, C85.2, C86.2, C87.2, C91.2, C92.2, IC7.2 (AGND), IC7.5 (DGND), IC7.10 (MD0), IC7.11 (MD1), IC7.12 (FMT); also elsewhere on the board
unnamed: C90.1, R26.2
unnamed: C93.1, R27.2
unnamed: C92.1, IC7.13 (VINL), R27.1
unnamed: C91.1, IC7.14 (VINR), R26.1
unnamed: C82.1, C83.1, IC7.1 (VREF)

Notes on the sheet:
filtre Anti aliasing pour éviter les perturbations du BT. f_c = 159 kHz, très au dessus de l'audible
Condensateurs de découplage

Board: 2 copper layers, 195 parts (0 on the bottom side), 123 nets, no tracks yet.
